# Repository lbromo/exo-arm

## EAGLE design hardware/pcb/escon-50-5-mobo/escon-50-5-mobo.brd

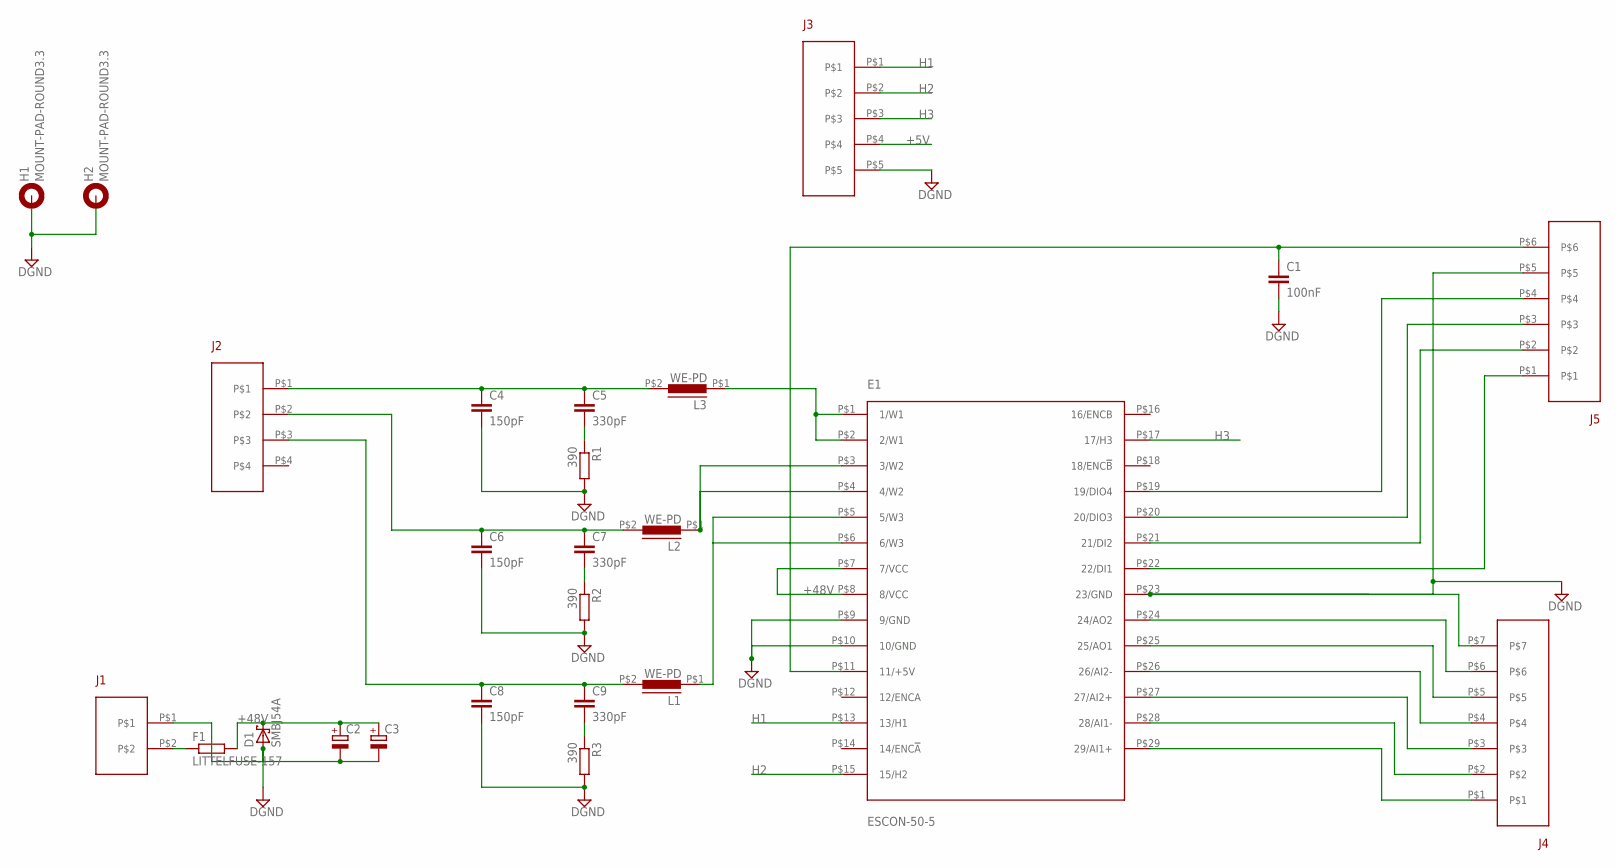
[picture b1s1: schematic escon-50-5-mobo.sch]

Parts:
C1: 100nF; C0805
C2, C3: CPOL-EUE5-13; E5-13
C4, C6, C8: 150pF; C0805
C5, C7, C9: 330pF; C0805
D1: SMBJ54A
E1: ESCON-50-5
F1: LITTELFUSE-157
H1, H2: MOUNT-PAD-ROUND3.3; 3,3-PAD
J1: PHOENIX-COMBICON-MCV-2POS
J2: PHOENIX-COMBICON-MCV-4POS
J3: PHOENIX-COMBICON-MCV-5POS
J4: PHOENIX-COMBICON-MCV-7POS
J5: PHOENIX-COMBICON-MCV-6POS
L1, L2, L3: WE-PD
R1, R2, R3: 390; R0805

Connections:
+5V: C1.1, E1.P$11 (11/+5V), J3.P$4, J5.P$6
+48V: C2.+, C3.+, D1.P$2 (C), E1.P$7 (7/VCC), E1.P$8 (8/VCC), F1.P$2 (2)
DGND: C1.2, C2.-, C3.-, C4.2, C6.2, C8.2, D1.P$1 (A), E1.P$9 (9/GND), E1.P$10 (10/GND), E1.P$23 (23/GND), H1.B3,3, H2.B3,3, J1.P$1, J3.P$5, J4.P$7, J5.P$5, R1.2, R2.2, R3.2
H1: E1.P$13 (13/H1), J3.P$1
H2: E1.P$15 (15/H2), J3.P$2
H3: E1.P$17 (17/H3), J3.P$3
unnamed: E1.P$22 (22/DI1), J5.P$1
unnamed: E1.P$21 (21/DI2), J5.P$2
unnamed: E1.P$20 (20/DIO3), J5.P$3
unnamed: E1.P$19 (19/DIO4), J5.P$4
unnamed: E1.P$1 (1/W1), E1.P$2 (2/W1), L3.P$1 (1)
unnamed: E1.P$3 (3/W2), E1.P$4 (4/W2), L2.P$1 (1)
unnamed: E1.P$24 (24/AO2), J4.P$6
unnamed: E1.P$25 (25/AO1), J4.P$5
unnamed: E1.P$26 (26/AI2-), J4.P$4
unnamed: E1.P$27 (27/AI2+), J4.P$3
unnamed: E1.P$28 (28/AI1-), J4.P$2
unnamed: E1.P$29 (29/AI1+), J4.P$1
unnamed: E1.P$5 (5/W3), E1.P$6 (6/W3), L1.P$1 (1)
unnamed: C5.2, R1.1
unnamed: F1.P$1 (1), J1.P$2
unnamed: C7.2, R2.1
unnamed: C9.2, R3.1
W1: C4.1, C5.1, J2.P$1, L3.P$2 (2)
W2: C6.1, C7.1, J2.P$2, L2.P$2 (2)
W3: C8.1, C9.1, J2.P$3, L1.P$2 (2)

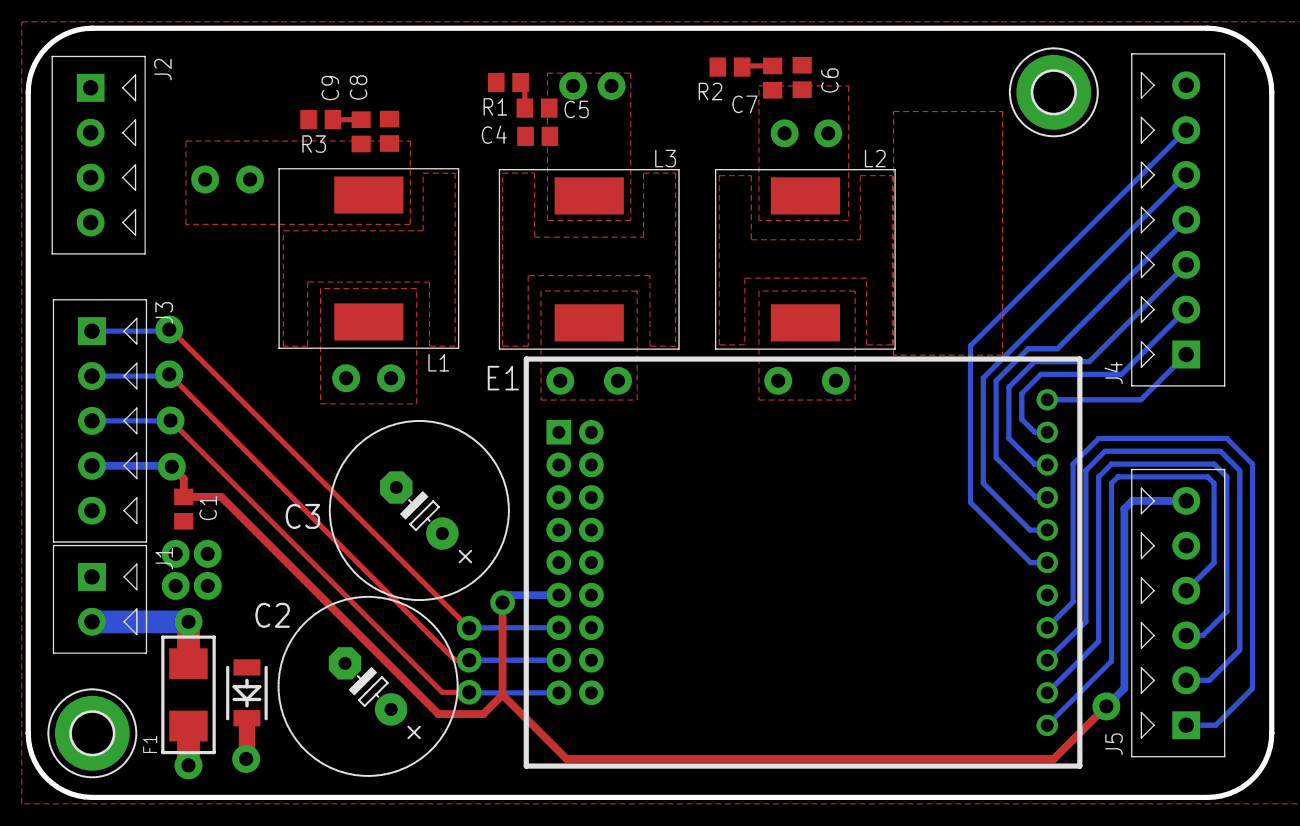
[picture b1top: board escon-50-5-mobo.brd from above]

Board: 2 copper layers, 97.0 x 60.0 mm, 25 parts (0 on the bottom side), 26 nets.

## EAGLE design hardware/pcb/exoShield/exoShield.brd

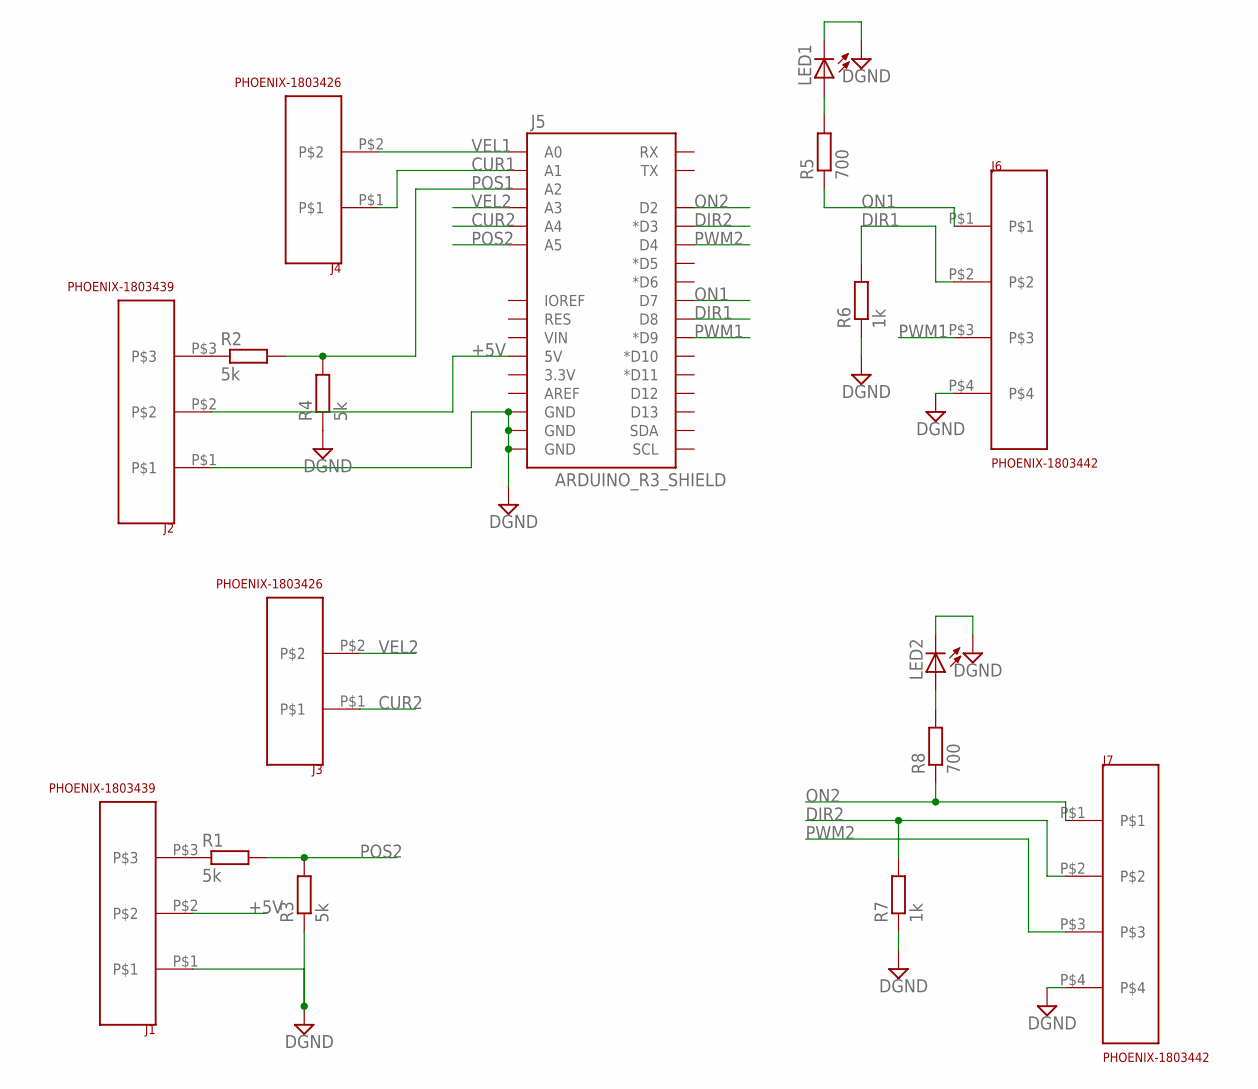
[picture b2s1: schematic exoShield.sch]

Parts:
J1, J2: PHOENIX-1803439
J3, J4: PHOENIX-1803426
J5: ARDUINO_R3_SHIELD; UNO_R3_SHIELD
J6, J7: PHOENIX-1803442
LED1, LED2: LED3MM
R1, R2, R3, R4: 5k; 0207/10
R5, R8: 700; 0207/10
R6, R7: 1k; 0207/10

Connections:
+5V: J1.P$2, J2.P$2, J5.5V
CUR1: J4.P$1, J5.A1
CUR2: J3.P$1, J5.A4
DGND: J1.P$1, J2.P$1, J5.GND@0 (GND), J5.GND@1 (GND), J5.GND@2 (GND), J6.P$4, J7.P$4, LED1.K (C), LED2.K (C), R3.1, R4.1, R6.1, R7.1
DIR1: J5.D8, J6.P$2, R6.2
DIR2: J5.D3 (*D3), J7.P$2, R7.2
unnamed: LED2.A, R8.2
unnamed: J2.P$3, R2.1
unnamed: J1.P$3, R1.1
unnamed: LED1.A, R5.2
ON1: J5.D7, J6.P$1, R5.1
ON2: J5.D2, J7.P$1, R8.1
POS1: J5.A2, R2.2, R4.2
POS2: J5.A5, R1.2, R3.2
PWM1: J5.D9 (*D9), J6.P$3
PWM2: J5.D4, J7.P$3
VEL1: J4.P$2, J5.A0
VEL2: J3.P$2, J5.A3

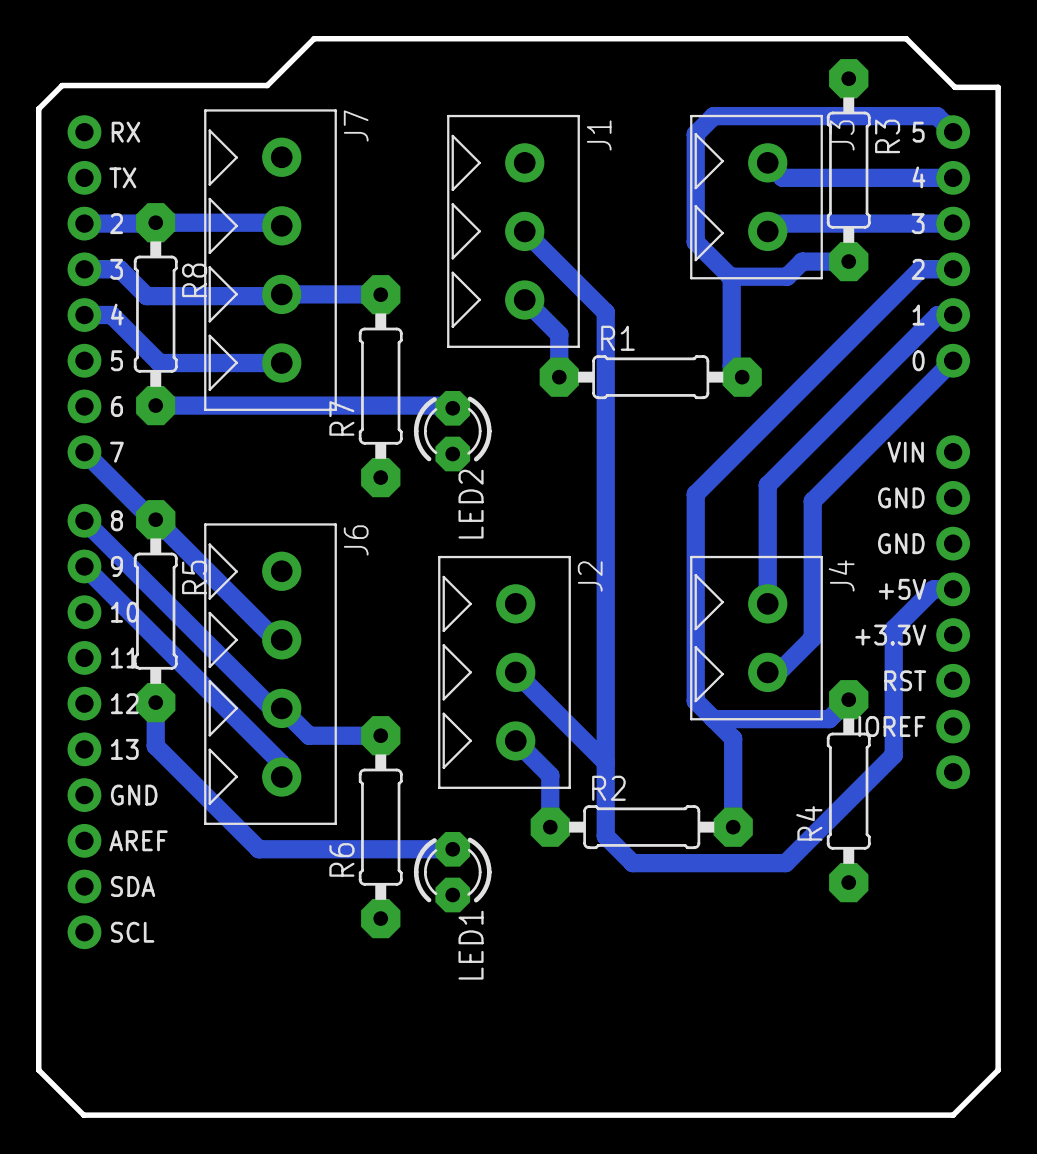
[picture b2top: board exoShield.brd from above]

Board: 2 copper layers, 53.3 x 59.8 mm, 17 parts (0 on the bottom side), 18 nets.

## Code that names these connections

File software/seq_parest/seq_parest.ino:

#define SAMPLE_F 100 // Hz
#define SAMPLE_T_MS 1000 * 1/SAMPLE_F
#define START_CHAR '$'
#define SHOULDER 1
#define ELBOW 2
#define MSG_LEN 10

bool led;

// Analog inputs
int pin_cur2 = A0;
int pin_vel2 = A1;
int pin_pos2 = A2;
int pin_cur1 = A3;
int pin_vel1 = A4;
int pin_pos1 = A5;


// Outputs
int  pin_on1 = 2;
int pin_dir1 = 3;
int pin_pwm1 = 5;
int  pin_on2 = 7;
int pin_dir2 = 8;
int pin_pwm2 = 9;


void setup(){

        analogReference(EXTERNAL);

        Serial.begin(115200);

        Serial.println("Scheduler running");
        
        led = 0;
        
        pinMode(pin_on1,OUTPUT);
        pinMode(pin_on2,OUTPUT);
        pinMode(pin_dir1,OUTPUT);
        pinMode(pin_dir2,OUTPUT);
        pinMode(pin_pwm1,OUTPUT);
        pinMode(pin_pwm2,OUTPUT);
        pinMode(13,OUTPUT);
        pinMode(12,OUTPUT);

        digitalWrite(13, led);
        analogWrite(pin_pwm1, 25);
        analogWrite(pin_pwm2, 25);

}

int getPos(int joint){

        if (joint == SHOULDER){
                return analogRead(pin_pos1);
        }
        else if (joint == ELBOW){
                return analogRead(pin_pos2);
        }
        else{
                return -1;
        }
}

int getCur(int joint){

        if (joint == SHOULDER){
                return analogRead(pin_cur1);
        }
        else if (joint == ELBOW){
                return analogRead(pin_cur2);
        }
        else{
                return -1;
        }
}

int getVel(int joint){

        if (joint == SHOULDER){
                return analogRead(pin_vel1);
        }
        else if (joint == ELBOW){
                return analogRead(pin_vel2);
        }
        else{
                return -1;
        }
}

void sendMeas(int joint, unsigned long time, int ang, int vel, int cur){

        char msg[50];
        Serial.println(START_CHAR);
        sprintf(msg, "%d,%lu,%d,%d,%d",joint,time,ang,vel,cur);
        Serial.println(msg);

}

void measure(){
        int vel1, cur1, ang1;
        int vel2, cur2, ang2;
        unsigned long time;

        ang1 = getPos(SHOULDER);
        cur1 = getCur(SHOULDER);
        vel1 = getVel(SHOULDER);
        time = millis();
        sendMeas(SHOULDER, time, ang1, vel1, cur1);

        ang2 = getPos(ELBOW);
        cur2 = getCur(ELBOW);
        vel2 = getVel(ELBOW);
        sendMeas(ELBOW, time, ang2, vel2, cur2);

}

void read_msg(){

        char dir1_buff[2], dir2_buff[2], on1_buff[2], on2_buff[2];
        char pwm1_buff[4], pwm2_buff[4];
        char chkbt;
        int on1, on2, dir1, dir2, pwm1, pwm2;
        int data_arr[6];

        // String terminators for later use with atoi()
        on1_buff[1] = '\0';
        on2_buff[1] = '\0';
        pwm1_buff[3] = '\0';
        pwm2_buff[3] = '\0';
        dir1_buff[1] = '\0';
        dir2_buff[1] = '\0';

        // Wait for start char..
        chkbt = Serial.read();
        while(chkbt != '$') {
                chkbt = Serial.read();
                digitalWrite(13,1);
        };
        
        digitalWrite(13,0);

        // Wait for whole message to be available
        while(Serial.available() < MSG_LEN) {
            digitalWrite(12,1);
                //Serial.println("waiting for rest of msg");
                //delay(500);
        };
        digitalWrite(12,0);

        // Read and convert all the shit!
        on1_buff[0] = Serial.read();
        dir1_buff[0] = Serial.read();
        
        for (int i = 0; i<3; i++){
                pwm1_buff[i] = Serial.read();
        }
        
        on1 = atoi(on1_buff);
        dir1 = atoi(dir1_buff);
        pwm1 = atoi(pwm1_buff);

        on2_buff[0] = Serial.read();
        dir2_buff[0] = Serial.read();
        
        for (int i = 0; i<3; i++){
                pwm2_buff[i] = Serial.read();
        }

        on2 = atoi(on2_buff);
        dir2 = atoi(dir2_buff);
        pwm2 = atoi(pwm2_buff);


        digitalWrite(pin_on1, on1);
        digitalWrite(pin_dir1, dir1);
        analogWrite(pin_pwm1, pwm1);
        digitalWrite(pin_on2, on2);
        digitalWrite(pin_dir2, dir2);
        analogWrite(pin_pwm2, pwm2);
        
}



void loop(){

	int starttime;
	starttime = int(millis());

  read_msg();
	measure();
  // delay(500);
	
	//delay(starttime+SAMPLE_T_MS-int(millis()));

//    digitalWrite(pin_on1,LOW);
//    digitalWrite(pin_on2,LOW);

}

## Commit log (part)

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2016-11-03 debug
2016-11-03 removed som of the stupid prints
2016-11-03 added nice prints
2016-11-04 made a protocol that seems to work
2016-11-04 trying timeout for stuff
2016-11-04 debug leds
2016-11-04 arduino debug
2016-11-04 activity leds
2016-11-04 serial prot
2016-11-04 sequential program fro logging shiat
2016-11-04 got pritns under control
2016-11-04 faster samples
2016-11-04 just to ba able to push
2016-11-04 tests
2016-11-07 seq parest
2016-11-08 newest logging programs
2016-11-08 gb thingy
2016-11-10 Greybox thingy works
2016-11-10 additions to parest scripst
2016-11-10 file names
2016-11-10 good file names
2016-11-11 maybe plotting?
2016-11-11 angle measurements
2016-11-11 Added current and velocity
2016-11-11 no more plots
2016-11-11 added shoulder curr and vel
2016-11-11 we also want negativ vel
2016-11-17 initial hill model
2016-11-17 latest parest software stuff
2016-11-17 Stupid hill model
2016-11-17 some plots
2016-11-18 Hill based mucsle - doesnt blow up :)
2016-11-21 Clean up in matlab
2016-11-21 python implementaion of hill model
2016-11-21 muscle len python niceness
2016-11-21 new gitignore
2016-11-21 New new gitignore
2016-11-21 stufff
2016-11-21 momentarm
2016-11-21 angle->len->force
2016-11-21 removbed print
2016-11-21 added exception
2016-11-21 calculate torque estimate
2016-11-21 plotting nice stuff
2016-11-22 combined stuff
2016-11-22 plot to 140 degrees
2016-11-22 useful little scripts. add to matlab path for maximum awesomenes
2016-11-22 It is slow, but we have Minv, G and V matrix structure :D
2016-11-22 forgot to add :)
2016-11-22 Refactor: Moved symbolic matrice construction out of the class. The matrices are now stored in a file, and read from file instead of regeneration on every run. constant parameters are also subbed in 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
2016-11-22 added pip requirements
2016-11-23 fast simulation in python
2016-11-25 Added pcb to git
2016-11-26 finally working
2016-11-28 model is working
2016-11-28 new parameter estimation stuff
2016-11-28 removed not useful files
2016-11-28 activationsignal
2016-11-28 added missing argument in lambda function
2016-11-28 Python2 fixes
2016-11-28 added file for full simulation
2016-11-28 removed exe flag
2016-11-29 Changed emg freq. to 100 Hz
2016-11-30 all ze new parest stuff
2016-12-01 parameter estimation with the entire dataset
2016-12-07 added comments
2016-12-07 fixed issue with arguments for shoulder calculations
2016-12-07 played around with friction coeffs
2016-12-07 added ipython notebook with PSO estimation
2016-12-07 cleaned up ipython notebook
2016-12-07 testing with ipython notebooks
2016-12-07 PSO in a fair implementation
2016-12-07 comments in pso
2016-12-07 major cleanup
2016-12-11 added more parest scripts
2016-12-13 Added newest revision script
2016-12-21 Friction coeff's --- i think there is a sign error
2017-01-30 something something
2017-02-07 ignore .pyc files
2017-02-07 removed .pyc files
2017-02-07 moved requirements.txt to a more proper location
2017-02-07 model mech
2017-02-07 Delete InertiaCalculations.m
    Not used anymore
2017-02-07 had flipped the motor interia (it was on the wrong joints)
2017-02-07 mech arm der nu virker i matlab- Wuhuuu
2017-02-07 new plots
2017-02-07 added emg filter stuff
2017-02-08 implemented EMG filtering
2017-02-08 at bit prettier
2017-02-08 nyt til muskelmodel
2017-02-09 muscle
2017-02-09 removed outputs
2017-02-09 using the bicect algorithm from scipy to find dLce and dLse numerically
    Lower tolerence of the on the online bisection calculations -- runs 4 times faster
2017-02-09 stripped output from ipython notebooks
2017-02-09 angles > 180 doesnt really make sense
2017-02-09 dont track ipynb_checkpoints
2017-02-13 observer pattern for activation signals
2017-02-13 new eagle file
2017-02-13 new useful scripts
2017-02-13 added files deleted by acident
2017-02-13 added files deleted by accident
2017-02-13 several_tests
2017-02-13 added a random width step function
2017-02-13 Now with random squares and sine sweep
2017-02-15 Now outputs loads of shit
2017-02-16 MORE LOGS!
2017-02-16 All mortens latest shit
2017-02-20 mat files with parameters
2017-02-20 modified logs
2017-02-21 mortens latest and greatest parest
2017-02-21 parest cleanup
2017-02-21 mat model
2017-02-21 both
2017-02-21 slight mods to model. Nothing serious
2017-02-21 added space for udoo software
2017-02-22 model
2017-02-22 ARRRG!
2017-02-22 updated angle cal
2017-02-23 FAILED
2017-02-23 added more logs
2017-02-27 try: excpet: around the bisect call.. If it fails we will assume that dLpe = dLce
2017-02-27 added an exploratory notebook where PyGMO fits parameters to muscle(s)
2017-02-28 parest stuff
2017-02-28 mortens updates
2017-02-28 nice little script for pwm 2 current conversion
2017-03-01 Now without scaling minimum owm
2017-03-01 LOGS!
2017-03-01 Morten attempted feedback linearization. Currently going to shit
2017-03-02 Mortens Simulator
2017-03-02 made folder for controllers
2017-03-03 mortens awesome feedback linearized controlelr
2017-03-06 NEW MSE SCRIPT
2017-03-06 hejssa
2017-03-06 now with goodnessOfFit()
2017-03-06 mortens controller experiments
2017-03-07 now using NMSE
2017-03-07 added some log files
2017-03-08 ØVVV!
2017-03-09 angle_input
2017-03-09 updated arduino control sketch, messenger now with ref
2017-03-10 rougth position estimate
2017-03-10 changed pin
2017-03-10 updated conversion for udoo
2017-03-10 morten solved overflowing int
2017-03-10 all mortens silly corrections
2017-03-13 Newest UDOO software. Now without truncating everything
2017-03-13 seperate stuff
2017-03-14 added matrix multiplication and matrix vector multiplication
2017-03-14 renaming and splitting out
2017-03-14 moved shit around
2017-03-14 updated stuff
2017-03-14 All the shit
2017-03-14 Simulation niceness.. Now with both mex, matlab and Arduino in the loopgst
2017-03-14 New matrix math and controller awesomeness
2017-03-14 corrections. New .gitignore
2017-03-14 fixed operator errors
2017-03-14 comments
2017-03-14 Revert "comments". Didn't mean to commit it :)
    This reverts commit dbe077652c2a9d1ac5fc3168e6478decebcc7e02.
2017-03-14 moved vector operators up the rest of the vector ctors
2017-03-15 Readded Matrixmath
2017-03-15 added copy ctor and assignment operator for matrices
2017-03-15 Default value for x0 and ref in exo_sim, messing around with def and ifndef, updated arduino_part to use Lasses c++ controller
2017-03-15 removed mat files, updated .gitignore to leave out symlinks
2017-03-16 Added admittance controller
2017-03-17 Added newest controller mods. Now with controller parameter struct. Also commented out some stuff in Matrix.cpp
2017-03-20 Latest changes to udoo
2017-03-20 Copy constructor and assignment operator is working on arduino
2017-03-20 output vector 'u' as a global variable
2017-03-21 Removed ktN from cur signal
2017-03-21 use afs
2017-03-21 added missing files
2017-03-22 I think I found out what is wrong. We need to multiply with 1/ktN
2017-03-23 cd into parest dir
2017-03-23 awesome
2017-03-23 save mse in the pickle
2017-03-23 fixed values
2017-03-23 stuff
2017-03-23 extract imu measurements
2017-03-23 fixed issue where the angle was ćut off too early of the last ext test
2017-03-23 fixed wrong angles stuff in mmre1.py
2017-03-23 maybe ready for parest
2017-03-24 Added the new pcb to git
2017-03-25 fixed for loop
2017-03-27 better?
2017-03-27 whoops
2017-03-27 megs
2017-03-27 added newest kicad
2017-03-27 small script for getting measurements into matlab
2017-03-27 fixed naming thing
2017-03-27 added stuff
2017-03-29 updated to run with 100 particles
2017-03-29 New N matrix! Also, added some compiler flags for things..
2017-03-30 1k 2 muscles
2017-04-05 first attempt at admittance control.. Simulation looks fine
2017-04-07 small changes in hardware files. Prolly just metadata. Updated parameter estimation scripts
2017-04-10 tested the pcb, made new parest meas. Everything seemed fine
2017-04-10 muscle model parameter verification
2017-04-17 Added an admittance filter thingy
2017-04-17 The UDOO software should be working now. Periodic control implemented with HWTIMERga model/useful_scripts/makeFIR.m!
2017-04-17 added python impl of an admittance PID filter
2017-04-17 added a wrapper function to create muscles based on a dict with paramters
2017-04-17 small script to cleanup the parest dicts
2017-04-17 ignore dat files
2017-04-17 Couldn't figure out how to 'live plot' with python3, so instead we broadcast the state vector over a udp socket, and the plotter scipt just plots from that state vector
2017-04-17 uhm. dunno
2017-04-17 2 muslce pickles
2017-04-17 updated mech model
2017-04-17 updated the full simulation
2017-04-17 removed all the stuff I accidentally added. I think
2017-04-17 made logging nice
2017-04-18 new controller
2017-04-19 moved arduino specific stuff out in hal
2017-04-19 1st attempt
2017-04-20 delayed matplotlib import
2017-04-20 pymyo can be installed with distutils -- no need to add it in path
2017-04-20 Serial stuff was really slow -- it is now in a Timer running each 0.01 second, and we just use the newest value when estimation joint torque
2017-04-20 100 hz sampling instead of 200
2017-04-20 moved default log decleration to a more appropiate place
2017-04-20 made some log files same length
2017-04-20 Mortens sim test script
2017-04-20 test fuck
2017-04-20 modified n vector to use correct model
2017-04-20 better
2017-04-20 verify with 2 muslces
2017-04-20 modified load_data
2017-04-21 added act signal to dat files for 4 muscles parest
2017-04-21 added act signal to dat files for 2 muscles parest
2017-04-21 added missing comma
2017-04-21 add emg to dat file, and print MSE
2017-04-21 added notebook to generate data file for estimatin chap with 4 muscles
2017-04-21 added notebook to generate data file for estimatin chap with 2 muscles
2017-04-21 changed data file name
2017-04-21 use space instead of a mixture of space and comma to seperate, and clean up headers
2017-04-25 controller sim script.. Is fairly shitty
2017-04-25 Revert "Maybe I fixed the angle"
    You didn't :) - This reverts commit 5307cb7b142d6fbd2eb06e49420e4862634ec03c.
2017-04-26 added stupid test as part of debugging the serial interface on the arduino
2017-04-26 appened state vector to include i_theta_s and i_theta_e
2017-04-26 T_SAMPLE_S should be a floating point number
2017-04-26 Fucking working
2017-04-26 Fixed an error where the copy constructor freed the memory of the original, invalidating the original
2017-04-26 use the old new N vector
2017-04-26 removed old junk
2017-04-26 ignore pickles
2017-04-26 cleanup and comments
2017-04-26 added functionality for minimal jerk
2017-04-26 changed ref print
2017-04-26 added log file for Lasse
2017-04-26 made better minjerk
2017-04-27 exo_sim now uses the reference in minjerk.csv
2017-04-27 I think I made PID correctly. Maybe we should add anti-windup
2017-04-27 Maybe the position is nice and fixed
2017-04-27 newest arduino sketch, works well
2017-04-27 newest messenger capable of using predefined path
2017-04-28 modification of exo_sim
2017-04-28 we need the M4 faster than the A9
2017-04-28 can now do 100 Hz
2017-04-28 faster logging -- using file as queue xD
2017-04-28 moved stuff around abit
2017-04-28 soft max on 90 deg
2017-04-28 added logs
2017-05-01 create a emg logger when ww are running
2017-05-01 made log files same length
2017-05-08 uses real angles ala mortens idea
2017-05-08 just notebooks
2017-05-10 admittance filter
2017-05-10 added new parametersscript that shold fit with model. I think
2017-05-10 Updated system matrices with 320mm link len
2017-05-10 changed link len to 320mm and removed an N
2017-05-10 negativ angles hack and updated admittance values
2017-05-10 we moved the arm a little
2017-05-11 add time to the emg logs
2017-05-17 more loggging
2017-05-17 rapport gains
2017-05-19 Made new n vector without gravity compensation
2017-05-19 I think the elbow should work now :)
2017-05-22 formatting
2017-05-22 use the normal controller
2017-05-23 update from monday
2017-05-29 updated so pagmo doesnt crash
2017-05-29 folder structure
2017-05-30 better logging
2017-06-12 increased resolution of reference
